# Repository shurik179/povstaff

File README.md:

# POV staff
This repository contains all files related to Persistence of Vision (POV) staff project. A detailed write-up of Version 1 of this project is available on  Instructables at [https://www.instructables.com/Persistence-of-Vision-LED-Staff/](https://www.instructables.com/Persistence-of-Vision-LED-Staff/); you can also find there photos  of the staff in action.

The latest version (as of June 1, 2023) is 4.1. It is documented at
https://povstaff.readthedocs.io

## Structure of this repository  
This repository is organized as follows:

* `docs`: documentation
* `code`: this directory contains the source code for the staff software
* `hardware`:  design files for the custom PCBs used in
  the project, as well as STEP files for the 3d printed components.
* `images`: sample image(s) and  `imagelist.txt` file

## Authors and license
This project was created by Alexander Kirillov <irobotics.store@gmail.com>; it is
based on [earlier work](https://learn.adafruit.com/pov-dotstar-double-staff) of
Phillip Burgess and Erin St Blaine from Adafruit. The project is available under
MIT license; see LICENSE file for details.

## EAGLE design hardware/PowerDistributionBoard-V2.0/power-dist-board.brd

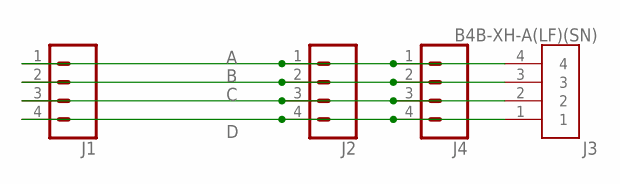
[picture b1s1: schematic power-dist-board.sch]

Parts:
J1, J2, J4: CONN_04; 1X04
J3: B4B-XH-A(LF)(SN); JST_B4B-XH-A(LF)(SN)

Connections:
A: J1.1, J2.1, J3.4, J4.1
B: J1.2, J2.2, J3.3, J4.2
C: J1.3, J2.3, J3.2, J4.3
D: J1.4, J2.4, J3.1, J4.4

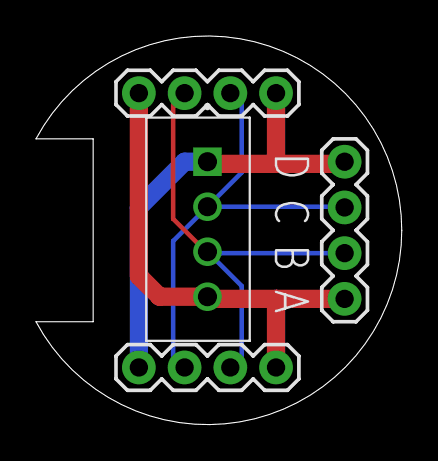
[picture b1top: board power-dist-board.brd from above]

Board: 2 copper layers, 20.3 x 21.6 mm, 4 parts (0 on the bottom side), 4 nets.

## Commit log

2020-10-16 Create LICENSE
2020-10-16 Initial commit of code and board design
2020-10-17 docs update
2020-10-21 code update; hardware directory update
2020-10-21 docs update - image orientation
2020-10-21 docs update - code README
2020-10-23 fixing bug in povstaff logic
2020-11-05 added image durations imagelist file
2020-11-05 Updated docs
2020-11-05 fixing minor typos
2020-11-05 added binaries
2020-11-06 release 1.0
2020-11-08 added formatter binary
2020-12-05 updated docs; spacer model
2020-12-05 Fixing the user guide
2021-02-27 updating gerbers
2021-12-02 added function to disable ItsyBitsy DotStar while show mode is active
2021-12-02 move images
2022-01-21 Added PDF of power distribution brd
2022-02-26 starting update for 2022 version
2022-03-07 starting work on docs
2022-03-08 docs updtae
2022-03-14 new switch spacer
2022-03-15 docs updating
2022-03-16 new photos for docs
2022-03-17 README updates
2022-03-21 adding PDB3.1; docs update
2022-03-26 fixing the bug with empty duration
2022-03-29 fix code to work with ItsyBitsy nRF52840
2022-03-31 docs updates
2022-04-01 minor doc fixes
2022-04-01 photos update
2022-04-03 created .gitattributes
2022-04-03 minor docs update
2022-04-03 annotated photo
2022-04-04 new version of spacer
2022-04-04 updating for version 3.1
2022-04-04 fixed file extension for controller wire-1a
2022-04-04 adding annotations to images
2022-04-04 final touches
2022-04-05 minor doc updates
2022-10-11 Updating for version 3.2
2022-10-13 updating kit content
2023-04-24 Version 4 - initial commit
2023-04-24 V4 cleanup
2023-04-24 hardware directory cleanup
2023-04-24 updating docs for v4
2023-04-24 docs - images update
2023-04-26 docs and 3d printed update
2023-04-26 docs cleanup
2023-05-12 new images for docs
2023-05-13 docs fix
2023-05-14 final assembly docs update
2023-05-14 docs minor fixes
2023-05-14 docs - image update
2023-05-14 typo fix
2023-05-14 software update
2023-05-16 dowel length fix
2023-05-16 docs work
2023-05-16 new photo for the docs
2023-05-18 added washers to bag F
2023-05-18 fixed copyright year
2023-05-19 minor docs updates
2023-06-01 V4 (#2)
    * Version 4 - initial commit
    * V4 cleanup
    * Update README.md
    * hardware directory cleanup
    * updating docs for v4
    * docs - images update
2023-06-01 new photos
2023-06-14 added handout
2023-07-03 minor update of 3d printed components
2023-10-24 minor changes
2023-10-24 readthedocs build system update
2024-01-02 updated charger spacer
2024-05-03 minor hardware updates
